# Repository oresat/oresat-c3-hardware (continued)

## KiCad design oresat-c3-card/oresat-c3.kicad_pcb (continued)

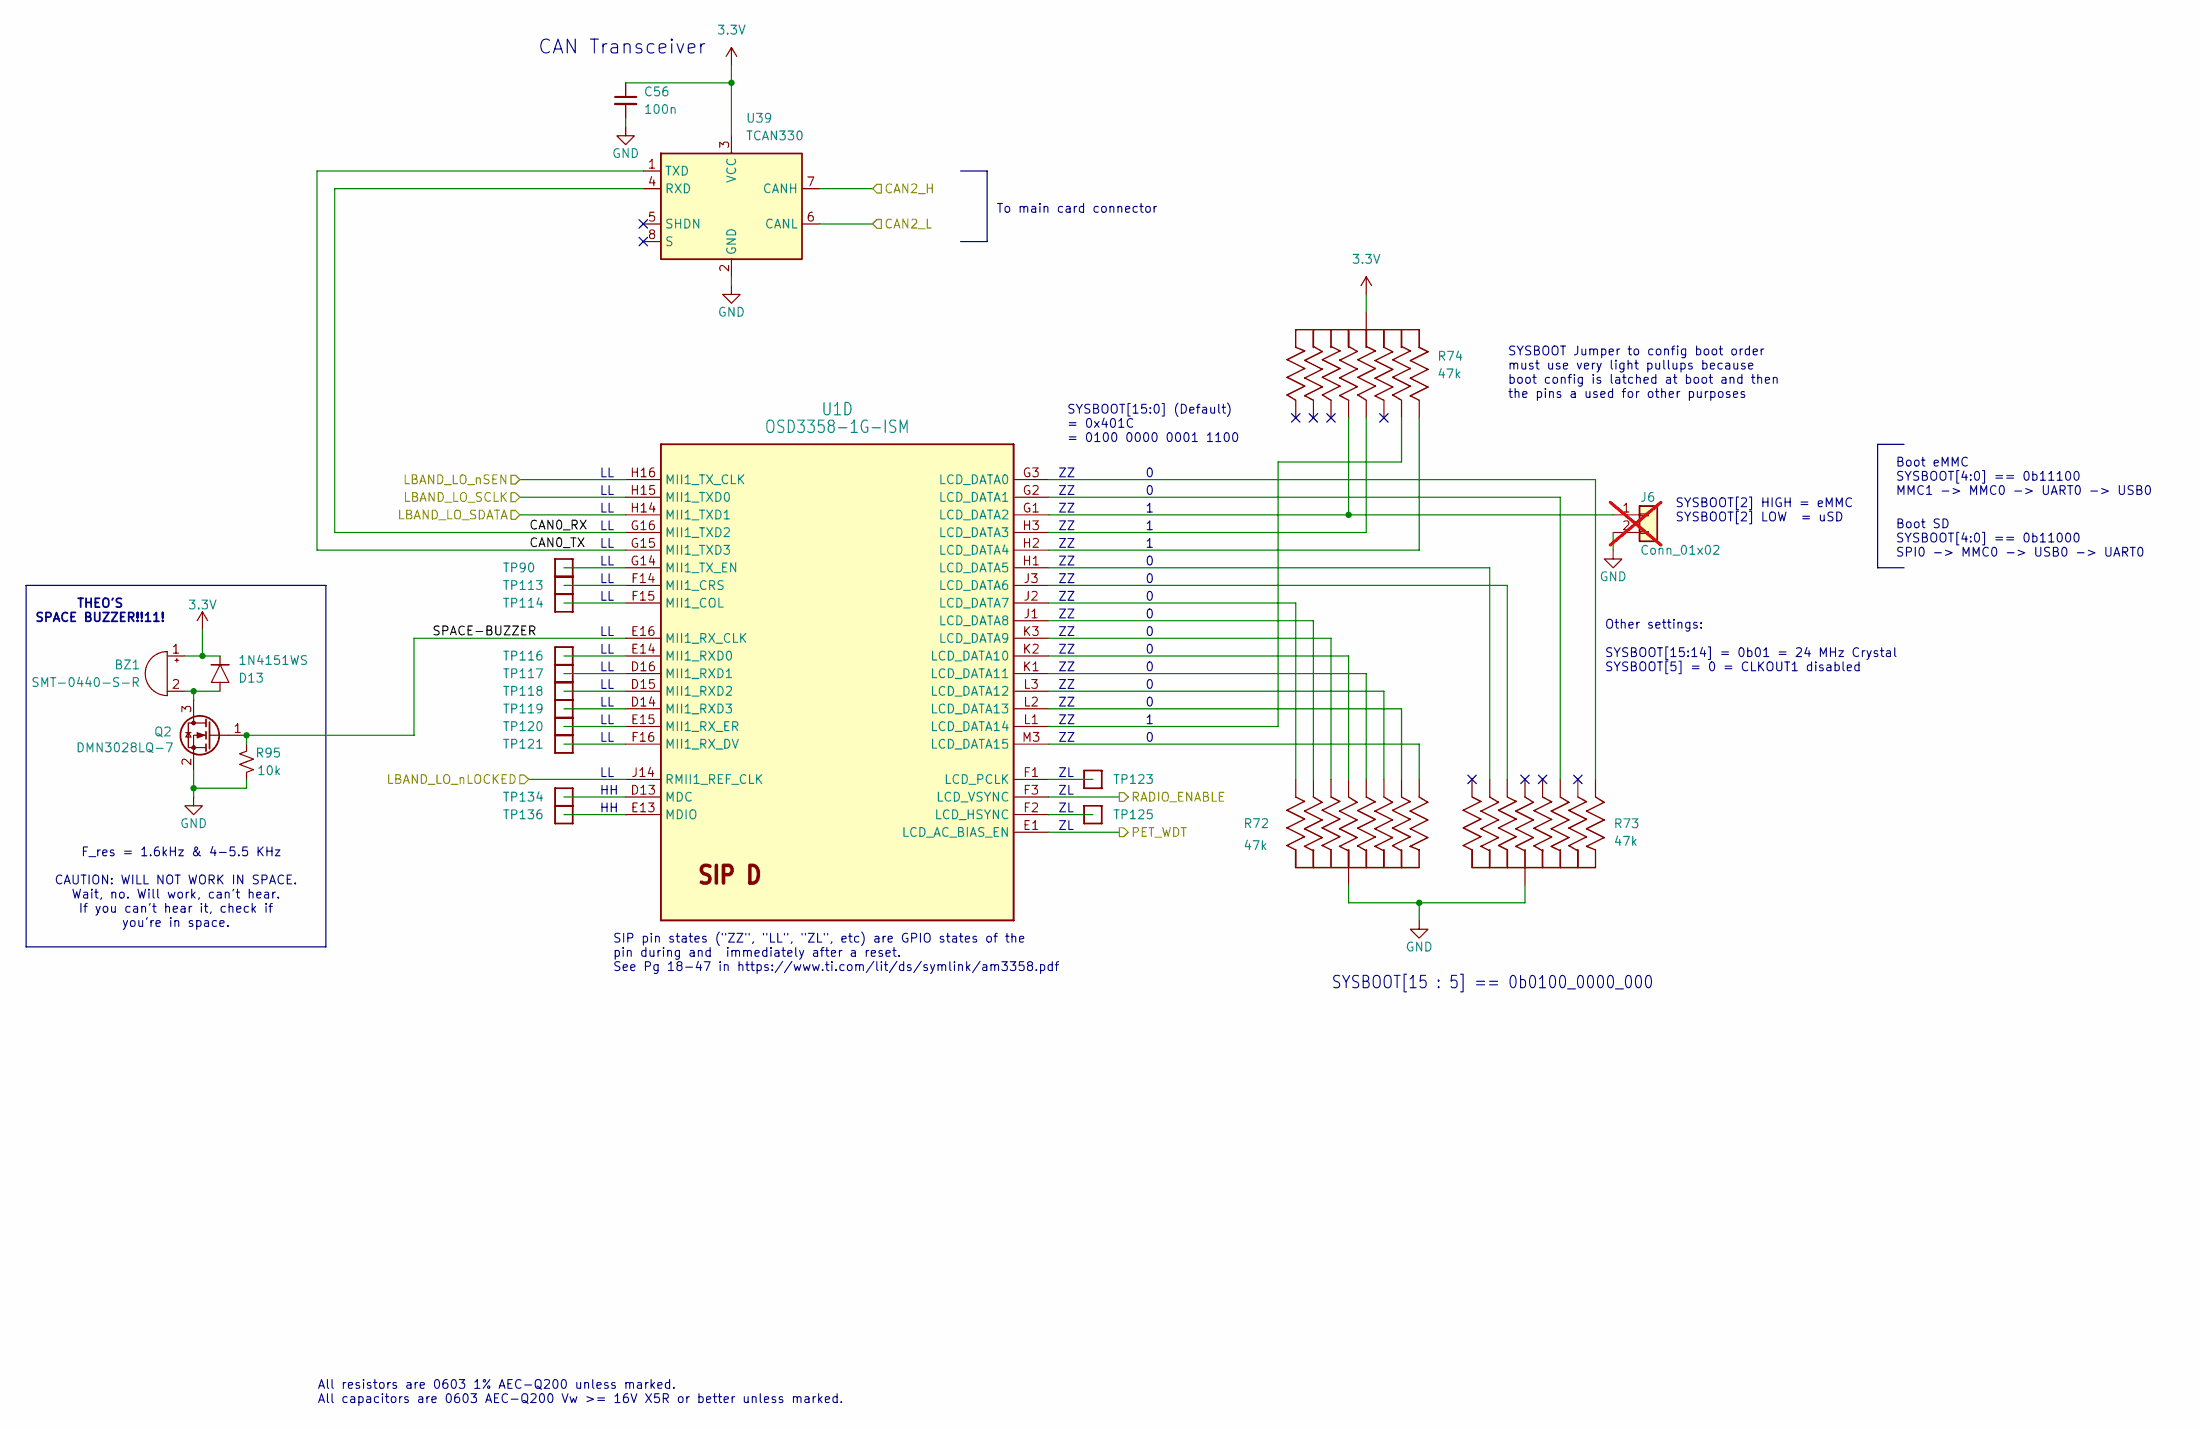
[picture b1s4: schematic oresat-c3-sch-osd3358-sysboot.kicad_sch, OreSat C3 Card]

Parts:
BZ1: SMT-0440-S-R; MPN SMT-0440-S-R
C56: 100n; 0603-C-NOSILK; MPN C0603C104K5RACAUTO
D13: 1N4151WS; D_SOD-323; MPN 1N4151WS-E3-08
J6: Conn_01x02; PinHeader_1x02_P2.54mm_Vertical; not fitted
Q2: DMN3028LQ-7; SOT-23-3; MPN DMN3028LQ-7
R72, R73, R74: 47k; Panasonic_Resistor_Array_EXBA10; MPN EXB-A10P473J
R95: 10k; 0603-C-NOSILK; MPN RMCF0603FT10K0
TP90, TP113, TP114, TP116, TP117, TP118, TP119, TP120, TP121, TP123, TP125, TP134, TP136: Test-Point; TestPoint_Pad_D1.0mm
U1: OSD3358-1G-ISM; U-Octavo-OSD335X-BGA-256; MPN OSD3358-512M-BSM
U39: TCAN330; SOT-23-8; MPN TCAN330GDCNT

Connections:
3.3V: BZ1.1 (+), C56.1, D13.1, R74.5 (55), R74.10 (55), U39.3 (VCC); also elsewhere on the board
/CAN2_H: U39.7 (CANH); also elsewhere on the board
/CAN2_L: U39.6 (CANL); also elsewhere on the board
/L Band/LBAND_LO_SCLK: U1.H15 (MII1_TXD0); also elsewhere on the board
/L Band/LBAND_LO_SDATA: U1.H14 (MII1_TXD1); also elsewhere on the board
/L Band/LBAND_LO_nLOCKED: U1.J14 (RMII1_REF_CLK); also elsewhere on the board
/L Band/LBAND_LO_nSEN: U1.H16 (MII1_TX_CLK); also elsewhere on the board
/OSD3358: SIP D/CAN0_RX: U1.G16 (MII1_TXD2), U39.4 (RXD)
/OSD3358: SIP D/CAN0_TX: U1.G15 (MII1_TXD3), U39.1 (TXD)
/OSD3358: SIP D/PET_WDT: U1.E1 (LCD_AC_BIAS_EN); also elsewhere on the board
/OSD3358: SIP D/RADIO_ENABLE: U1.F3 (LCD_VSYNC); also elsewhere on the board
/OSD3358: SIP D/SPACE-BUZZER: Q2.1 (G), R95.1, U1.E16 (MII1_RX_CLK)
GND: C56.2, J6.2, Q2.2 (S), R72.5 (55), R72.10 (55), R73.5 (55), R73.10 (55), R95.2, U39.2 (GND); also elsewhere on the board
unnamed: BZ1.2 (-), D13.2, Q2.3 (D)
unnamed: J6.1, R74.8 (88), U1.G1 (LCD_DATA2)
unnamed: R72.1 (11), U1.M3 (LCD_DATA15)
unnamed: R72.2 (22), U1.L3 (LCD_DATA12)
unnamed: R72.3 (33), U1.K2 (LCD_DATA10)
unnamed: R72.4 (44), U1.J1 (LCD_DATA8)
unnamed: R72.6 (66), U1.J2 (LCD_DATA7)
unnamed: R72.7 (77), U1.K3 (LCD_DATA9)
unnamed: R72.8 (88), U1.K1 (LCD_DATA11)
unnamed: R72.9 (99), U1.L2 (LCD_DATA13)
unnamed: R73.1 (11), U1.G3 (LCD_DATA0)
unnamed: R73.2 (22), U1.G2 (LCD_DATA1)
unnamed: R73.4 (44), U1.H1 (LCD_DATA5)
unnamed: R73.7 (77), U1.J3 (LCD_DATA6)
unnamed: R74.3 (33), U1.H3 (LCD_DATA3)
unnamed: R74.4 (44), U1.L1 (LCD_DATA14)
unnamed: R74.6 (66), U1.H2 (LCD_DATA4)
unnamed: TP125.1 (1_1), U1.F2 (LCD_HSYNC)
unnamed: TP123.1 (1_1), U1.F1 (LCD_PCLK)
unnamed: TP134.1 (1_1), U1.D13 (MDC)
unnamed: TP136.1 (1_1), U1.E13 (MDIO)
unnamed: TP114.1 (1_1), U1.F15 (MII1_COL)
unnamed: TP113.1 (1_1), U1.F14 (MII1_CRS)
unnamed: TP116.1 (1_1), U1.E14 (MII1_RXD0)
unnamed: TP117.1 (1_1), U1.D16 (MII1_RXD1)
unnamed: TP118.1 (1_1), U1.D15 (MII1_RXD2)
unnamed: TP119.1 (1_1), U1.D14 (MII1_RXD3)
unnamed: TP121.1 (1_1), U1.F16 (MII1_RX_DV)
unnamed: TP120.1 (1_1), U1.E15 (MII1_RX_ER)
unnamed: TP90.1 (1_1), U1.G14 (MII1_TX_EN)

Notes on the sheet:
THEO'S SPACE BUZZER!!11!
SYSBOOT[2] HIGH = eMMC SYSBOOT[2] LOW = uSD
SIP pin states ("ZZ", "LL", "ZL", etc) are GPIO states of the pin during and immediately after a reset. See Pg 18-47 in https://www.ti.com/lit/ds/symlink/am3358.pdf
Boot SD SYSBOOT[4:0] == 0b11000 SPI0 -> MMC0 -> USB0 -> UART0
All resistors are 0603 1% AEC-Q200 unless marked. All capacitors are 0603 AEC-Q200 Vw >= 16V X5R or better unless marked.
Boot eMMC SYSBOOT[4:0] == 0b11100 MMC1 -> MMC0 -> UART0 -> USB0
SYSBOOT[15:0] (Default) = 0x401C = 0100 0000 0001 1100
CAN Transceiver
SYSBOOT Jumper to config boot order must use very light pullups because boot config is latched at boot and then the pins a used for other purposes
F_res = 1.6kHz & 4-5.5 KHz
Other settings: SYSBOOT[15:14] = 0b01 = 24 MHz Crystal SYSBOOT[5] = 0 = CLKOUT1 disabled
SYSBOOT[15 : 5] == 0b0100_0000_000
To main card connector
CAUTION: WILL NOT WORK IN SPACE. Wait, no. Will work, can't hear. If you can't hear it, check if you're in space.

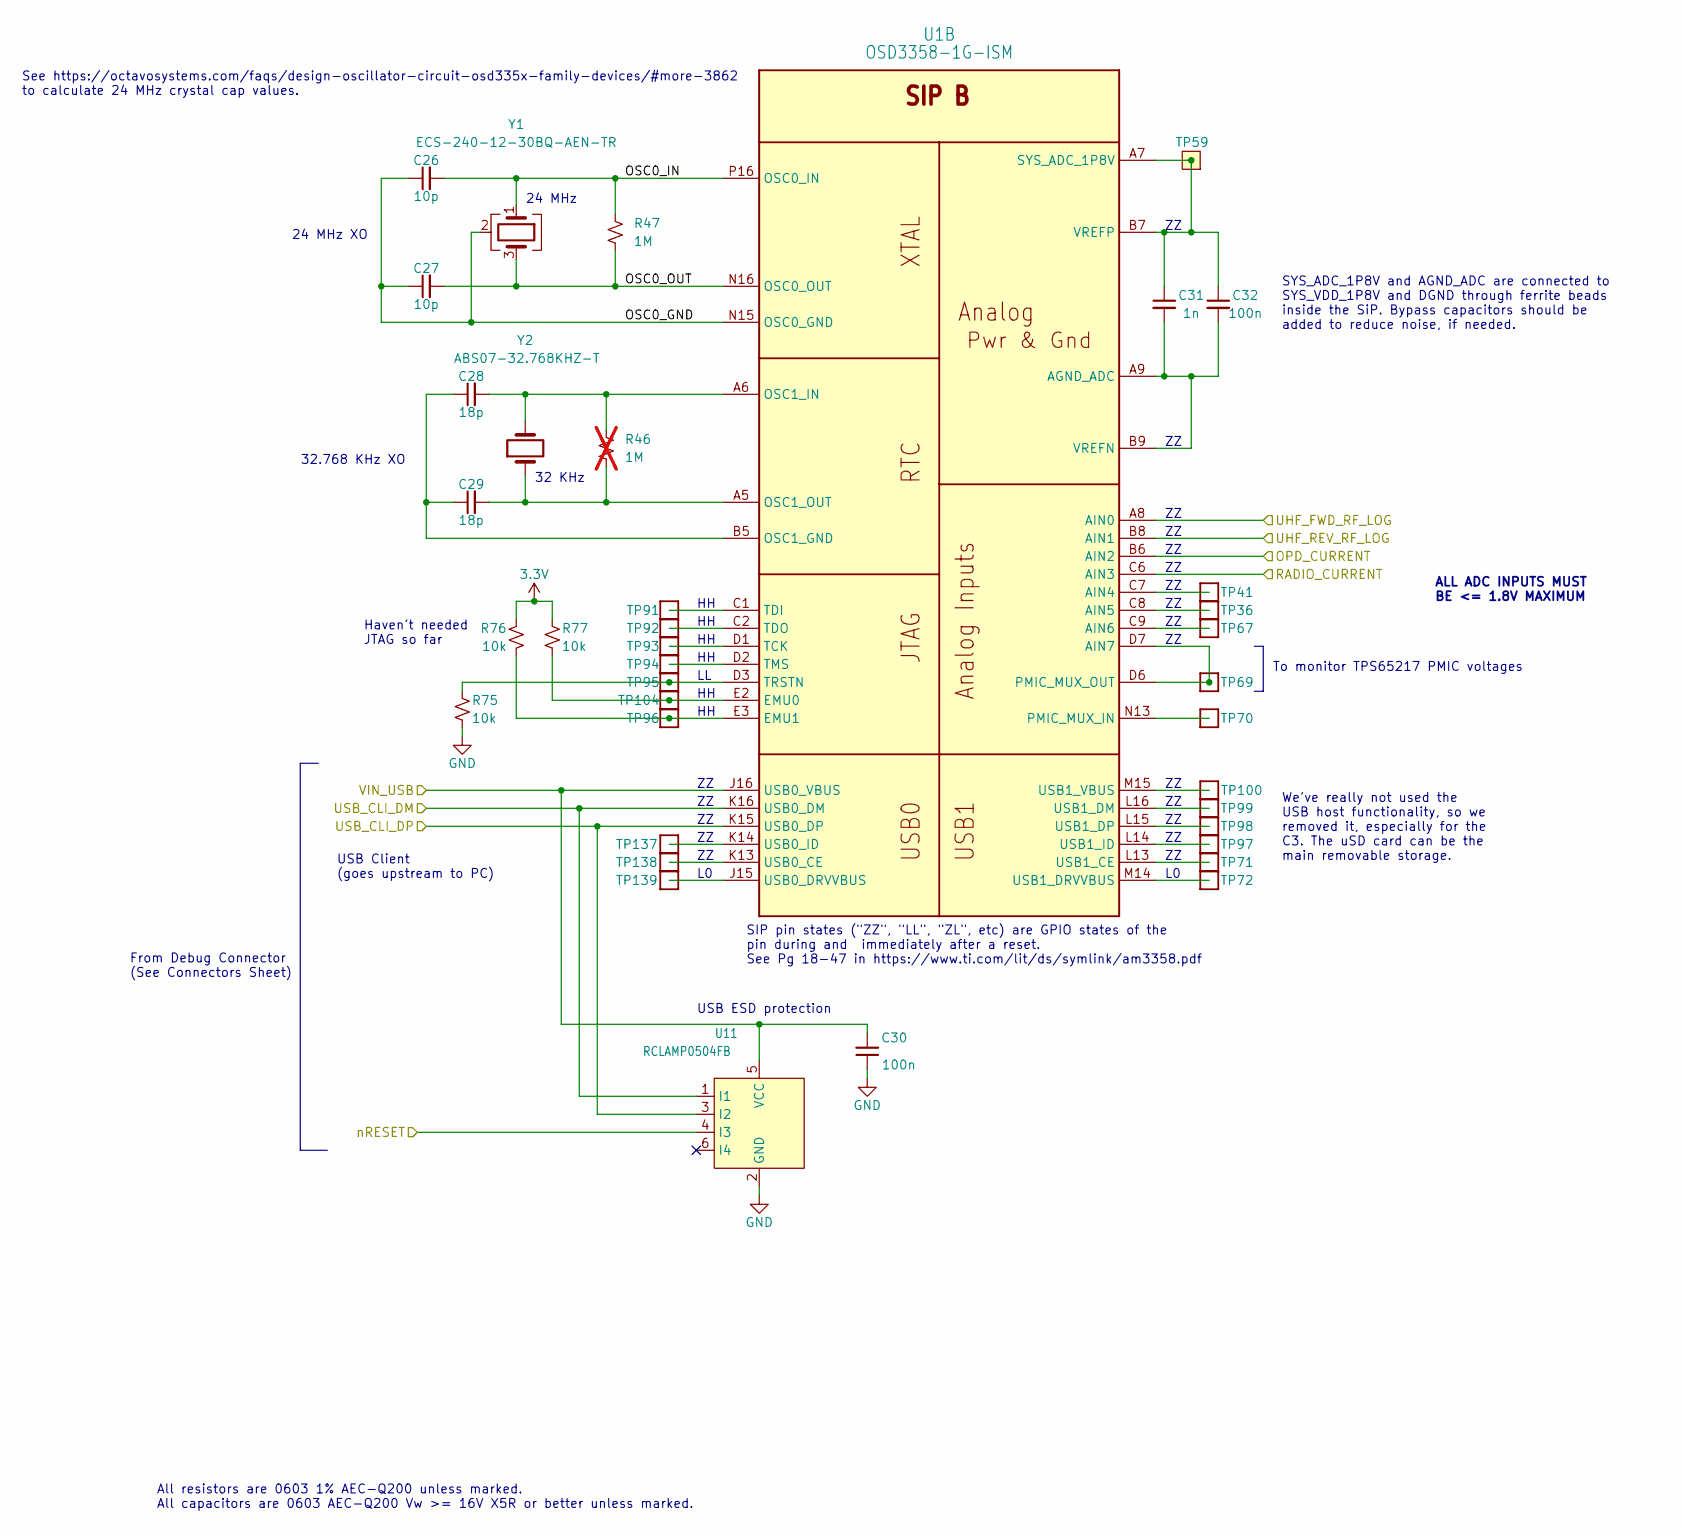
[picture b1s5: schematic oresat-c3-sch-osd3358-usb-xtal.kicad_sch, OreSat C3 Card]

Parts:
C26, C27: 10p; 0603-C-NOSILK; MPN C0603C100J1GACAUTO
C28, C29: 18p; 0603-C-NOSILK; MPN C0603C180F5GACAUTO
C30, C32: 100n; 0603-C-NOSILK; MPN C0603C104K5RACAUTO
C31: 1n; 0603-C-NOSILK; MPN C0603C102J5RACAUTO
R46: 1M; R_0603_1608Metric; not fitted
R47: 1M; 0603-C-NOSILK; MPN RMCF0603FG1M00
R75, R76, R77: 10k; 0603-C-NOSILK; MPN RMCF0603FT10K0
TP36, TP41, TP67, TP69, TP70, TP71, TP72, TP91, TP92, TP93, TP94, TP95, TP96, TP97, TP98, TP99, TP100, TP104, TP137, TP138, TP139: Test-Point; TestPoint_Pad_D1.0mm
TP59: Test-Point; TestPoint-0.75mm-th
U1: OSD3358-1G-ISM; U-Octavo-OSD335X-BGA-256; MPN OSD3358-512M-BSM
U11: RCLAMP0504FB; SOT-363_SC-70-6; MPN RCLAMP0504FBTCT
Y1: ECS-240-12-30BQ-AEN-TR; CRYSTAL-5X3.2-4SMD; MPN ECS-240-12-30BQ-AEN-TR
Y2: ABS07-32.768KHZ-T; CRYSTAL_3.2X1.5; MPN ABS07-32.768KHZ-T

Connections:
3.3V: R76.1, R77.1; also elsewhere on the board
/OPD and I2C Peripherals/OPD_CURRENT: U1.B6 (AIN2); also elsewhere on the board
/OSD3358: SIP A/nRESET: U11.4 (I3); also elsewhere on the board
/OSD3358: SIP B/OSC0_GND: C26.1, C27.1, U1.N15 (OSC0_GND), Y1.2 (G), Y1.4 (G)
/OSD3358: SIP B/OSC0_IN: C26.2, R47.1, U1.P16 (OSC0_IN), Y1.1
/OSD3358: SIP B/OSC0_OUT: C27.2, R47.2, U1.N16 (OSC0_OUT), Y1.3
/OSD3358: SIP B/RADIO_CURRENT: U1.C6 (AIN3); also elsewhere on the board
/OSD3358: SIP B/UHF_FWD_RF_LOG: U1.A8 (AIN0); also elsewhere on the board
/OSD3358: SIP B/UHF_REV_RF_LOG: U1.B8 (AIN1); also elsewhere on the board
/USB_CLI_DM: U1.K16 (USB0_DM), U11.1 (I1); also elsewhere on the board
/USB_CLI_DP: U1.K15 (USB0_DP), U11.3 (I2); also elsewhere on the board
/VIN_USB: C30.2, U1.J16 (USB0_VBUS), U11.5 (VCC); also elsewhere on the board
GND: C30.1, R75.2, U11.2 (GND); also elsewhere on the board
unnamed: C31.2, C32.2, U1.A9 (AGND_ADC), U1.B9 (VREFN)
unnamed: TP41.1 (1_1), U1.C7 (AIN4)
unnamed: TP36.1 (1_1), U1.C8 (AIN5)
unnamed: TP67.1 (1_1), U1.C9 (AIN6)
unnamed: TP69.1 (1_1), U1.D6 (PMIC_MUX_OUT), U1.D7 (AIN7)
unnamed: R77.2, TP95.1 (1_1), U1.E2 (EMU0)
unnamed: R76.2, TP96.1 (1_1), U1.E3 (EMU1)
unnamed: C28.1, C29.1, U1.B5 (OSC1_GND)
unnamed: C28.2, R46.1, U1.A6 (OSC1_IN), Y2.2
unnamed: C29.2, R46.2, U1.A5 (OSC1_OUT), Y2.1
unnamed: TP70.1 (1_1), U1.N13 (PMIC_MUX_IN)
unnamed: C31.1, C32.1, TP59.1 (1_1), U1.A7 (SYS_ADC_1P8V), U1.B7 (VREFP)
unnamed: TP93.1 (1_1), U1.D1 (TCK)
unnamed: TP91.1 (1_1), U1.C1 (TDI)
unnamed: TP92.1 (1_1), U1.C2 (TDO)
unnamed: TP94.1 (1_1), U1.D2 (TMS)
unnamed: R75.1, TP104.1 (1_1), U1.D3 (TRSTN)
unnamed: TP138.1 (1_1), U1.K13 (USB0_CE)
unnamed: TP139.1 (1_1), U1.J15 (USB0_DRVVBUS)
unnamed: TP137.1 (1_1), U1.K14 (USB0_ID)
unnamed: TP71.1 (1_1), U1.L13 (USB1_CE)
unnamed: TP99.1 (1_1), U1.L16 (USB1_DM)
unnamed: TP98.1 (1_1), U1.L15 (USB1_DP)
unnamed: TP72.1 (1_1), U1.M14 (USB1_DRVVBUS)
unnamed: TP97.1 (1_1), U1.L14 (USB1_ID)
unnamed: TP100.1 (1_1), U1.M15 (USB1_VBUS)

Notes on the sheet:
32.768 KHz XO
ALL ADC INPUTS MUST BE <= 1.8V MAXIMUM
To monitor TPS65217 PMIC voltages
SIP pin states ("ZZ", "LL", "ZL", etc) are GPIO states of the pin during and immediately after a reset. See Pg 18-47 in https://www.ti.com/lit/ds/symlink/am3358.pdf
See https://octavosystems.com/faqs/design-oscillator-circuit-osd335x-family-devices/#more-3862 to calculate 24 MHz crystal cap values.
24 MHz XO
32 KHz
Haven't needed JTAG so far
All resistors are 0603 1% AEC-Q200 unless marked. All capacitors are 0603 AEC-Q200 Vw >= 16V X5R or better unless marked.
We've really not used the USB host functionality, so we removed it, especially for the C3. The uSD card can be the main removable storage.
USB Client (goes upstream to PC)
24 MHz
USB ESD protection
SYS_ADC_1P8V and AGND_ADC are connected to SYS_VDD_1P8V and DGND through ferrite beads inside the SiP. Bypass capacitors should be added to reduce noise, if needed.
From Debug Connector (See Connectors Sheet)

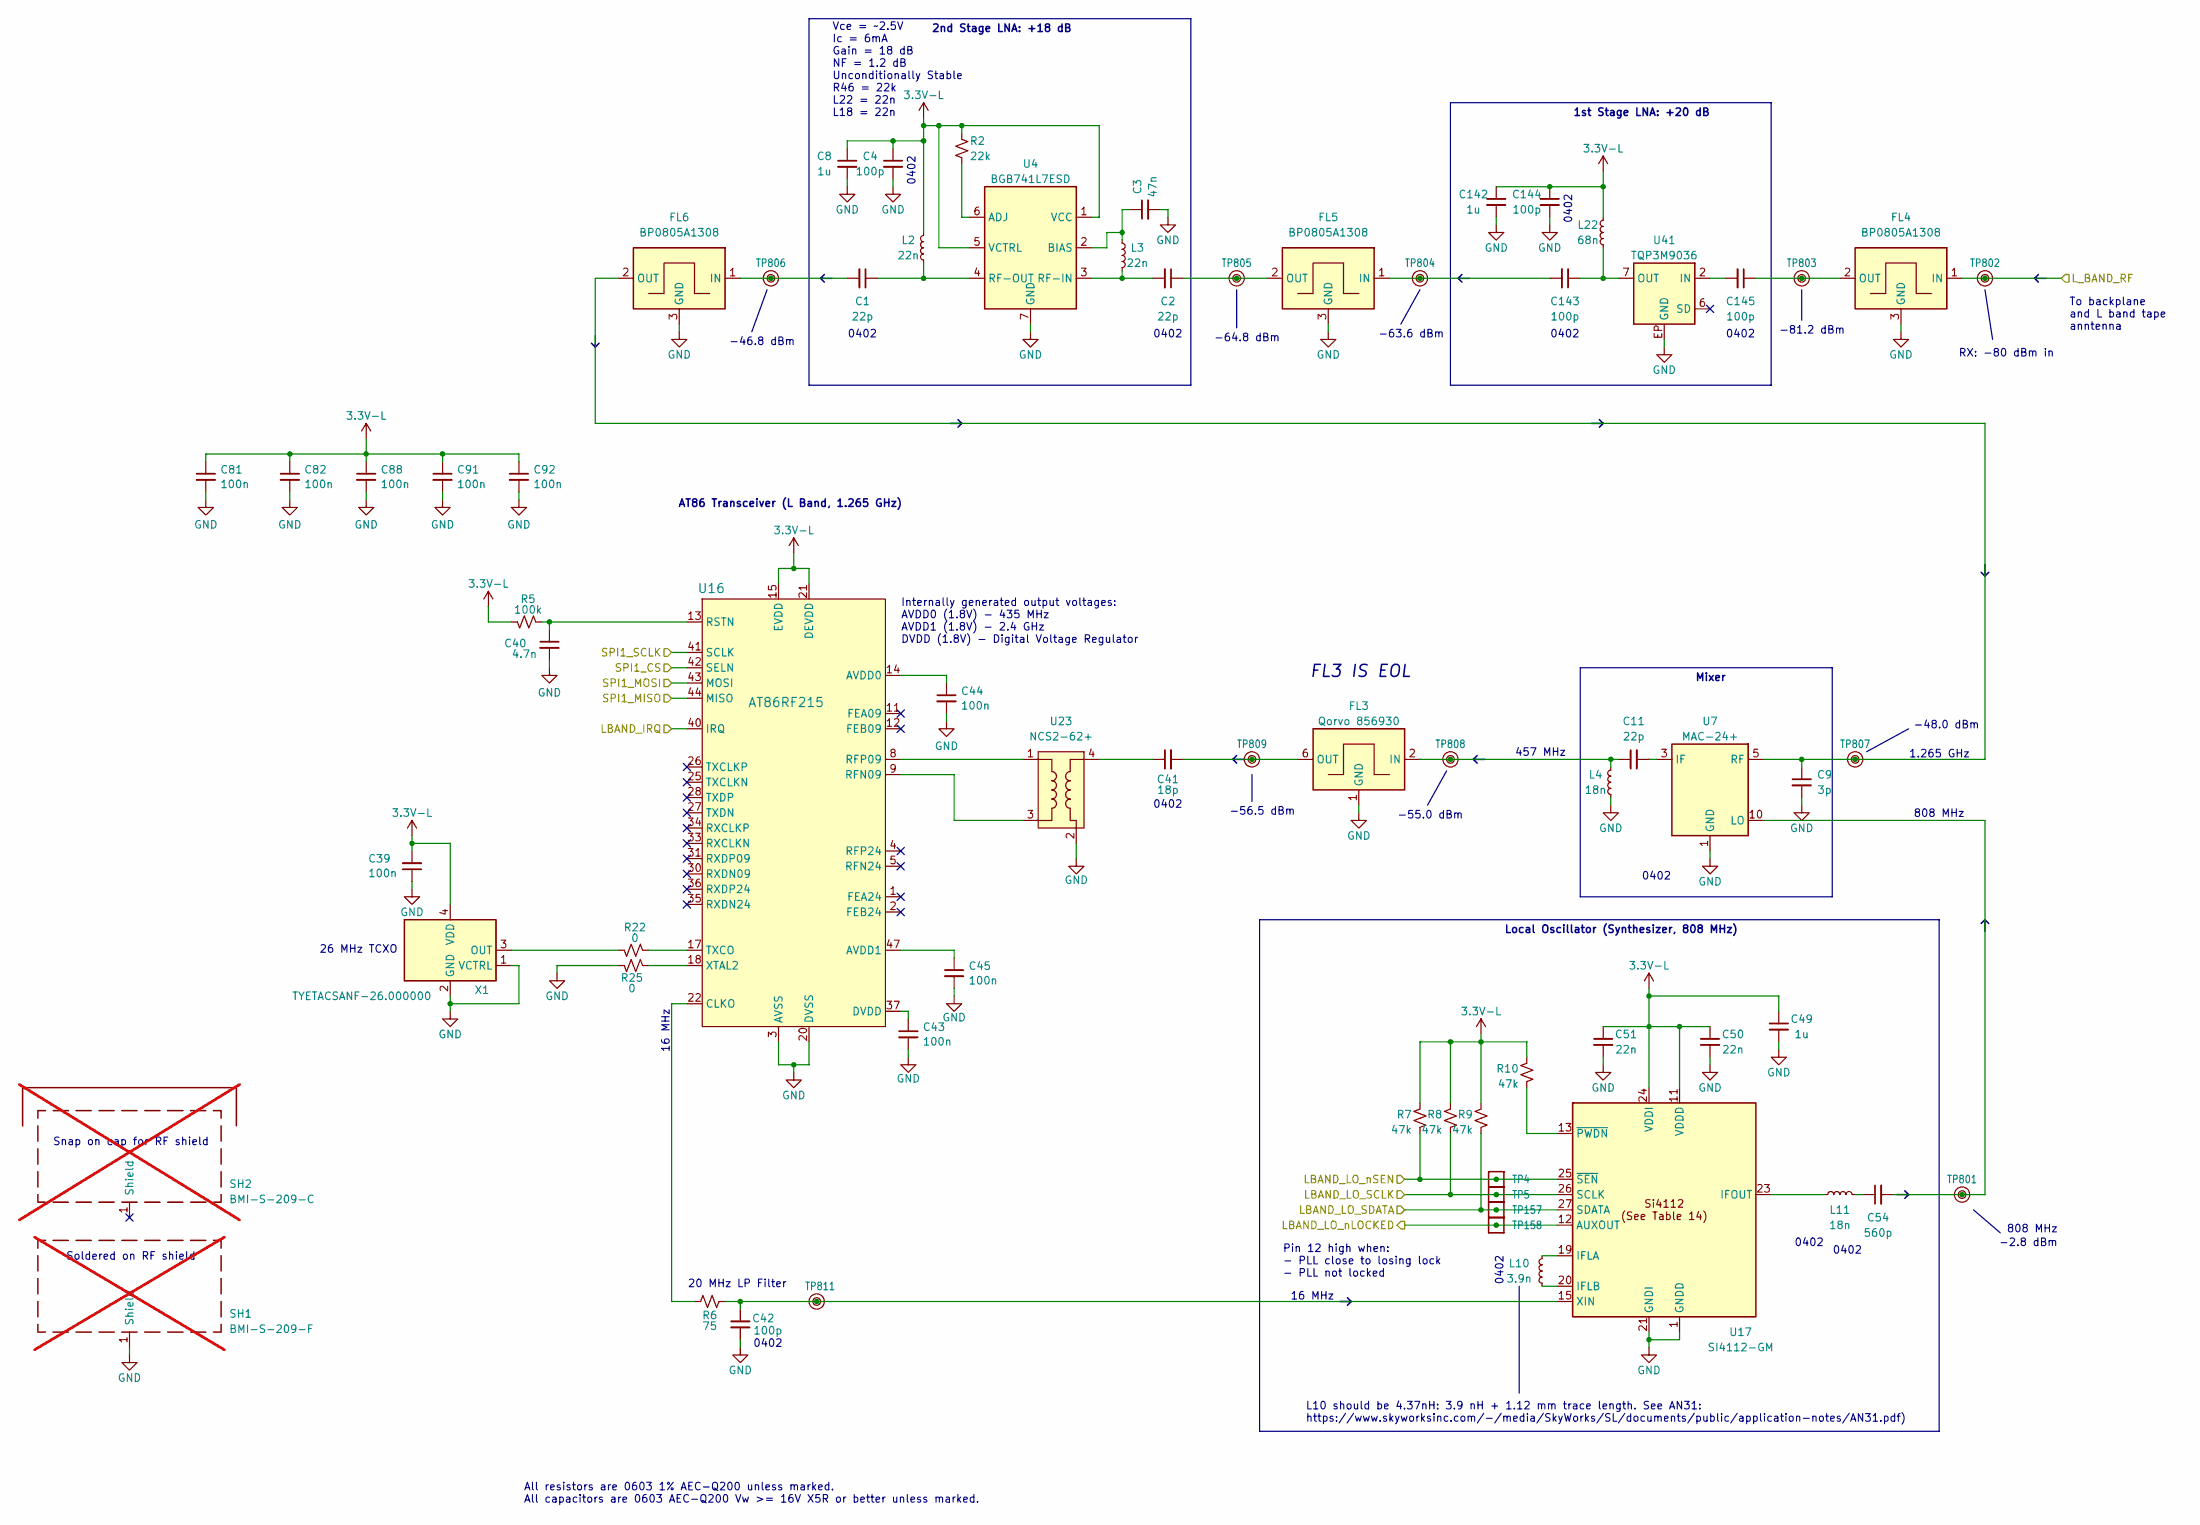
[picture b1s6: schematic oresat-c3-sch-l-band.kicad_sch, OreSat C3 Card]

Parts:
C1, C2, C11: 22p; 0402-B-NOSILK; MPN CBR04C220J5GACAUTO
C3: 47n; 0603-C-NOSILK; MPN C0603C473K5RACAUTO
C4, C42, C143, C144, C145: 100p; 0402-B-NOSILK; MPN C0402C101J5GACAUTO
C8, C49, C142: 1u; 0603-C-NOSILK; MPN GRT188R71E105KE13D
C9: 3p; 0402-B-NOSILK; MPN GCQ1555C1H3R0CB01D
C39, C43, C44, C45, C81, C82, C88, C91, C92: 100n; 0603-C-NOSILK; MPN C0603C104K5RACAUTO
C40: 4.7n; 0603-C-NOSILK; MPN C0603C472K5RACAUTO
C41: 18p; 0402-B-NOSILK; MPN CBR04C180J5GACAUTO
C50, C51: 22n; 0603-C-NOSILK; MPN C0603C223K1RACAUTO
C54: 560p; 0402-B-NOSILK; MPN C0402C561J5GACAUTO
FL3: Qorvo 856930; 856930-saw-filter; MPN 856930
FL4, FL5, FL6: BP0805A1308; BP0805; MPN BP0805A1308ASTR
L2, L3: 22n; L_0603_1608Metric; MPN LQW18AN22NG0ZD
L4, L11: 18n; L_0402_1005Metric; MPN 0402HP-18NXGL
L10: 3.9n; L_0402_1005Metric; MPN 0402CS-3N9XGL
L22: 68n; L_0603_1608Metric; MPN LQW18AN68NG8ZD
R2: 22k; 0603-C-NOSILK; MPN RMCF0603FT22K0
R5: 100k; 0603-C-NOSILK; MPN RMCF0603FT100K
R6: 75; 0603-C-NOSILK; MPN RMCF0603FT75R0
R7, R8, R9, R10: 47k; 0603-C-NOSILK; MPN RMCF0603FT47K0
R22, R25: 0; 0603-C-NOSILK; MPN RMCF0603ZT0R00
SH1: BMI-S-209-F; Laird_Technologies_BMI-S-209-F_29.36x18.50mm; MPN BMI-S-209-F; not fitted
SH2: BMI-S-209-C; MPN BMI-S-209-C; not fitted
TP4, TP5, TP157, TP158: Test-Point; TestPoint_Pad_D1.0mm
TP801, TP802, TP803, TP804, TP805, TP806, TP807, TP808, TP809, TP811: TestPoint_RF_Probe
U4: BGB741L7ESD; Infineon-PG-TSLP-7-LNA; MPN BGB741L7ESDE6327XTSA1‎
U7: MAC-24+; MPN MAC-24+
U16: AT86RF215; QFN-48-1EP_7x7mm_P0.5mm_EP5.6x5.6mm; MPN AT86RF215-ZUR
U17: SI4112-GM; QFN-28-1EP_5x5mm_P0.5mm_EP3.35x3.35mm_ThermalVias; MPN SI4112-D-GM
U23: NCS2-62+; 2450FB15A050E_JOT; MPN NCS2-62+
U41: TQP3M9036; U-Qorvo-TQP3M9036-QFN-8-MO-220E; MPN TQP3M9036
X1: TYETACSANF-26.000000; X_TCXO_SMD_Taitien_2.5x2.0mm; MPN TYETACSANF-26.000000

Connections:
3.3V-L: C4.1, C8.1, C39.2, C49.1, C50.1, C51.1, C81.1, C82.1, C88.1, C91.1, C92.1, C142.1, C144.1, L2.1, L22.1, R2.1, R5.2, R7.1, R8.1, R9.1, R10.1, U4.1 (VCC), U4.5 (VCTRL), U16.15 (EVDD), U16.21 (DEVDD), U16.29 (DEVDD), U16.39 (DEVDD), U16.46 (EVDD), U17.11 (VDDD), U17.17 (VDDD), U17.24 (VDDI), X1.4 (VDD); also elsewhere on the board
/L Band/LBAND_IRQ: U16.40 (IRQ); also elsewhere on the board
/L Band/LBAND_LO_SCLK: R8.2, TP5.1 (1_1), U17.26 (SCLK); also elsewhere on the board
/L Band/LBAND_LO_SDATA: R9.2, TP157.1 (1_1), U17.27 (SDATA); also elsewhere on the board
/L Band/LBAND_LO_nLOCKED: TP158.1 (1_1), U17.12 (AUXOUT); also elsewhere on the board
/L Band/LBAND_LO_nSEN: R7.2, TP4.1 (1_1), U17.25 (~SEN); also elsewhere on the board
/L Band/SPI1_CS: U16.42 (SELN); also elsewhere on the board
/L Band/SPI1_MISO: U16.44 (MISO); also elsewhere on the board
/L Band/SPI1_MOSI: U16.43 (MOSI); also elsewhere on the board
/L Band/SPI1_SCLK: U16.41 (SCLK); also elsewhere on the board
/L_BAND_RF: FL4.1 (IN), TP802.1 (1_1); also elsewhere on the board
GND: C3.2, C4.2, C8.2, C9.2, C39.1, C40.2, C42.2, C43.2, C44.2, C45.2, C49.2, C50.2, C51.2, C81.2, C82.2, C88.2, C91.2, C92.2, C142.2, C144.2, FL3.1 (GND), FL3.3 (GND), FL3.4 (GND), FL3.5 (GND), FL3.7 (GND), FL3.8 (GND), FL4.3 (GND), FL4.4 (GND), FL5.3 (GND), FL5.4 (GND), FL6.3 (GND), FL6.4 (GND), L4.2, R25.2, SH1.1 (Shield_1), U4.7 (GND), U7.1 (GND), U7.2 (GND), U7.4 (GND), U7.6 (GND), U7.7 (GND), U7.8 (GND), U7.9 (GND), U16.3 (AVSS), U16.6 (AVSS), U16.7 (AVSS), U16.10 (AVSS), U16.16 (AVSS), U16.19 (AVSS), U16.20 (DVSS), U16.23 (DVSS), U16.24 (DVSS), U16.32 (DVSS), U16.38 (DVSS), U16.45 (AVSS), U16.48 (AVSS), U16.49 (AVSS), U17.1 (GNDD), U17.2 (GNDD), U17.3 (GNDD), U17.4 (GNDD), U17.5 (GNDD), U17.6 (GNDD), U17.7 (GNDD), U17.8 (GNDD), U17.9 (GNDD), U17.10 (GNDD), U17.14 (GNDD), U17.16 (GNDD), U17.18 (GNDD), U17.21 (GNDI), U17.22 (GNDI), U17.28 (GNDD), U17.29 (GNDD), U23.2 (GND), U23.6 (GND), U41.EP (GND), X1.1 (VCTRL), X1.2 (GND); also elsewhere on the board
unnamed: C41.1, U23.4
unnamed: C54.1, L11.2
unnamed: C11.1, FL3.2 (IN), L4.1, TP808.1 (1_1)
unnamed: C41.2, FL3.6 (OUT), TP809.1 (1_1)
unnamed: C145.1, FL4.2 (OUT), TP803.1 (1_1)
unnamed: C143.2, FL5.1 (IN), TP804.1 (1_1)
unnamed: C2.1, FL5.2 (OUT), TP805.1 (1_1)
unnamed: C1.2, FL6.1 (IN), TP806.1 (1_1)
unnamed: C9.1, FL6.2 (OUT), TP807.1 (1_1), U7.5 (RF)
unnamed: R2.2, U4.6 (ADJ)
unnamed: C3.1, L3.1, U4.2 (BIAS)
unnamed: C2.2, L3.2, U4.3 (RF-IN)
unnamed: C1.1, L2.2, U4.4 (RF-OUT)
unnamed: C11.2, U7.3 (IF)
unnamed: C54.2, TP801.1 (1_1), U7.10 (LO)
unnamed: C44.1, U16.14 (AVDD0)
unnamed: C45.1, U16.47 (AVDD1)
unnamed: R6.1, U16.22 (CLKO)
unnamed: C43.1, U16.37 (DVDD)
unnamed: U16.9 (RFN09), U23.3
unnamed: U16.8 (RFP09), U23.1
unnamed: C40.1, R5.1, U16.13 (RSTN)
unnamed: R22.1, U16.17 (TXCO)
unnamed: R25.1, U16.18 (XTAL2)
unnamed: L10.1, U17.19 (IFLA)
unnamed: L10.2, U17.20 (IFLB)
unnamed: L11.1, U17.23 (IFOUT)
unnamed: C42.1, R6.2, TP811.1 (1_1), U17.15 (XIN)
unnamed: R10.2, U17.13 (~PWDN)
unnamed: C145.2, U41.2 (IN)
unnamed: C143.1, L22.2, U41.7 (OUT)
unnamed: R22.2, X1.3 (OUT)

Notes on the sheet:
0402
-56.5 dBm
-46.8 dBm
Pin 12 high when: - PLL close to losing lock - PLL not locked
RX: -80 dBm in
FL3 IS EOL
AT86 Transceiver (L Band, 1.265 GHz)
Internally generated output voltages: AVDD0 (1.8V) - 435 MHz AVDD1 (1.8V) - 2.4 GHz DVDD (1.8V) - Digital Voltage Regulator
Vce = ~2.5V Ic = 6mA Gain = 18 dB NF = 1.2 dB Unconditionally Stable R46 = 22k L22 = 22n L18 = 22n
L10 should be 4.37nH: 3.9 nH + 1.12 mm trace length. See AN31: https://www.skyworksinc.com/-/media/SkyWorks/SL/documents/public/application-notes/AN31.pdf)
2nd Stage LNA: +18 dB
1.265 GHz
-2.8 dBm
808 MHz
1st Stage LNA: +20 dB
26 MHz TCXO
-81.2 dBm
To backplane and L band tape anntenna
All resistors are 0603 1% AEC-Q200 unless marked. All capacitors are 0603 AEC-Q200 Vw >= 16V X5R or better unless marked.
457 MHz
-55.0 dBm
-64.8 dBm
20 MHz LP Filter
-63.6 dBm
16 MHz
Snap on cap for RF shield
Mixer
Local Oscillator (Synthesizer, 808 MHz)
Soldered on RF shield
-48.0 dBm

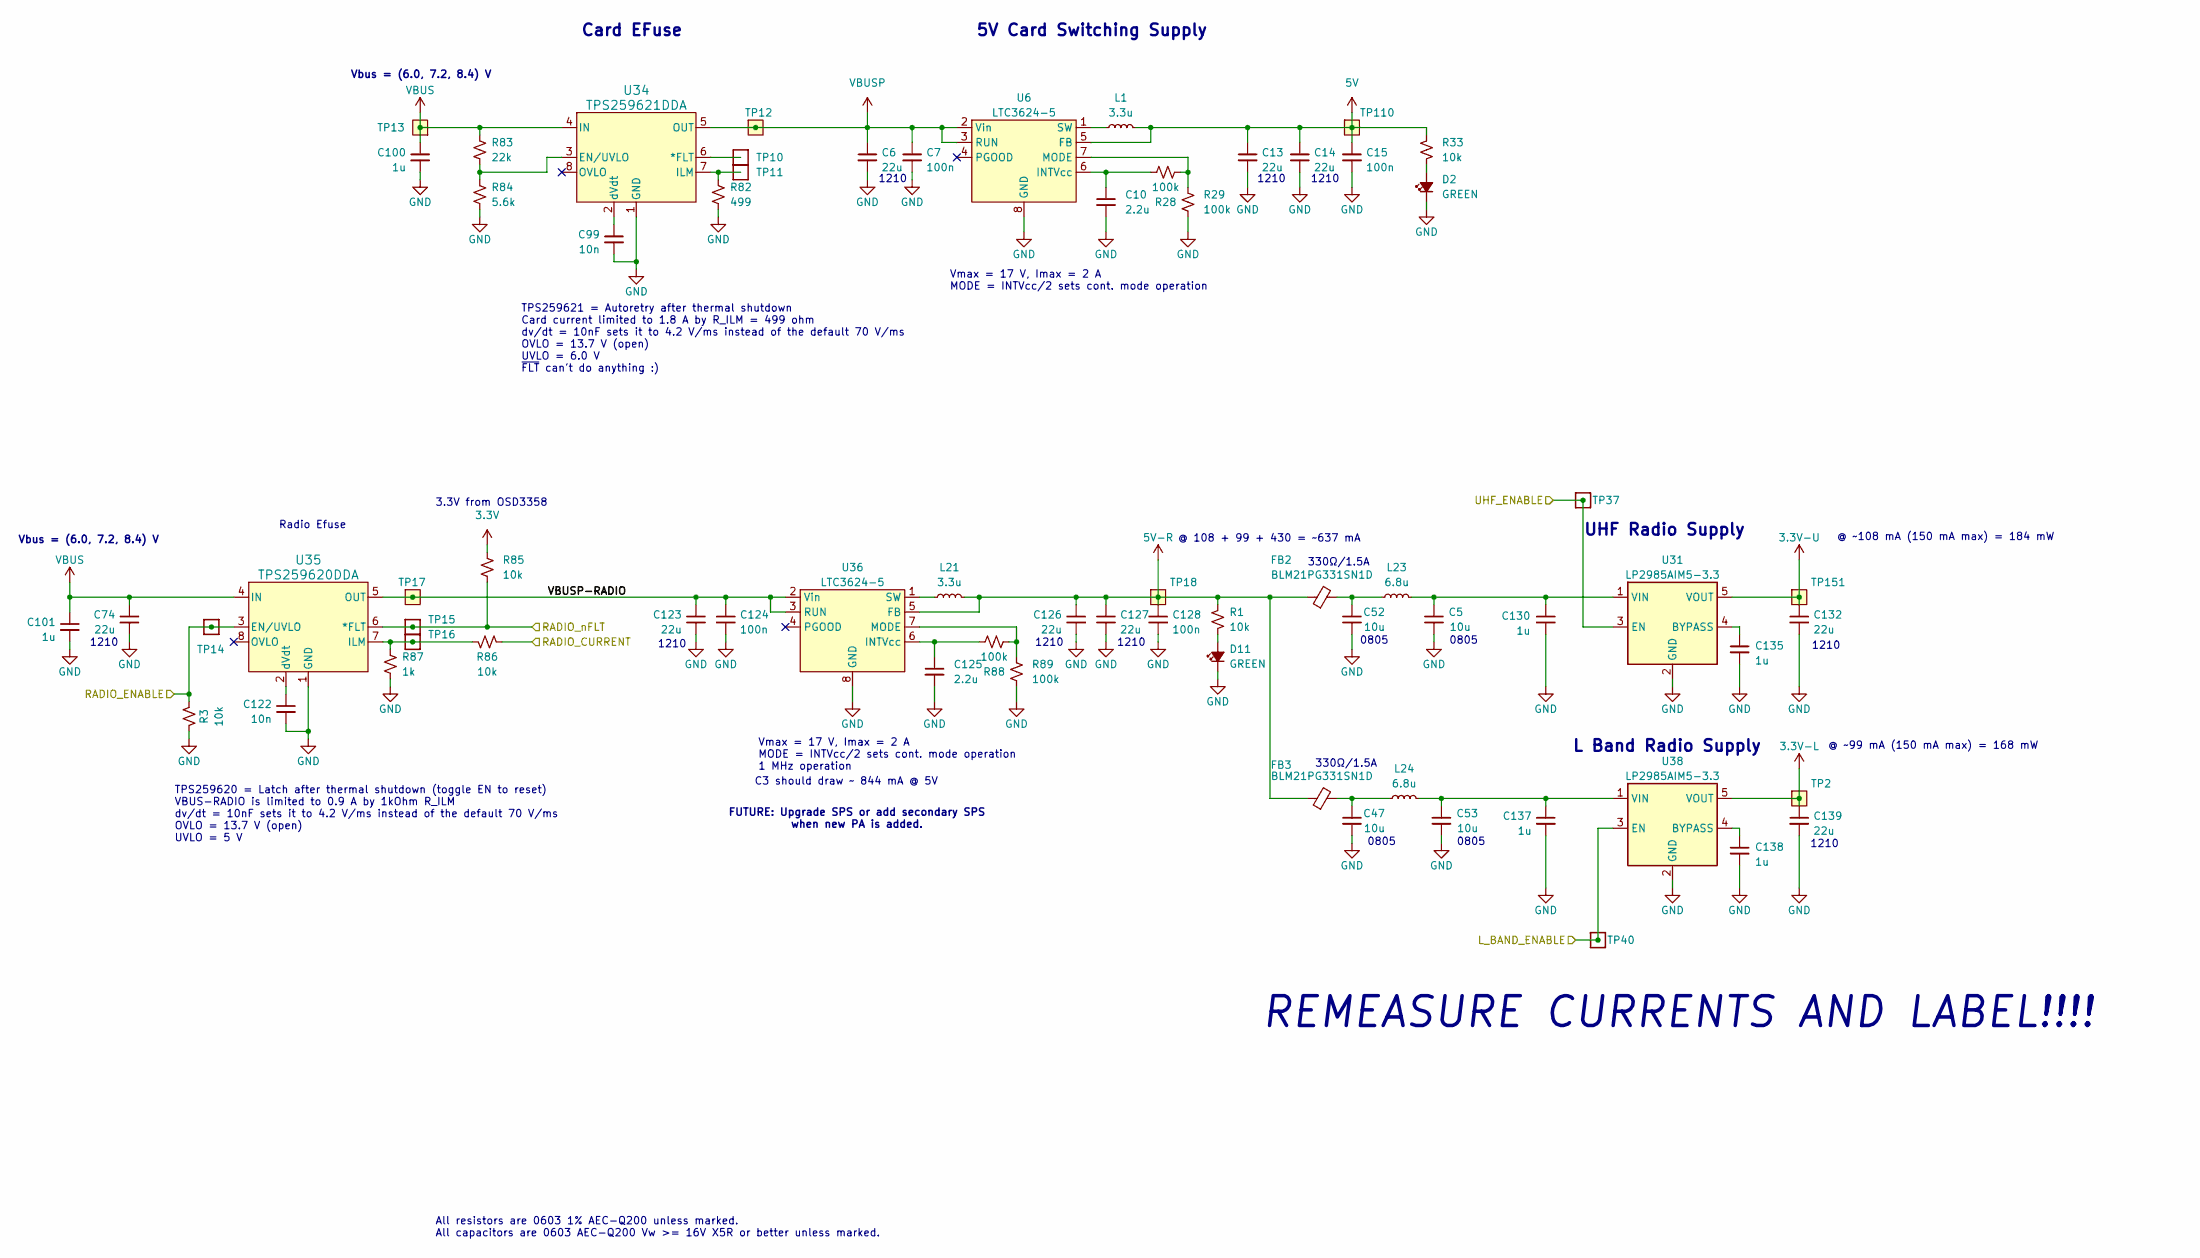
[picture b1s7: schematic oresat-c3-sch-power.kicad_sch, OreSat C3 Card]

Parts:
C5, C47, C52, C53: 10u; 0805-C-NOSILK; MPN GRT21BC71E106KE13K
C6, C13, C14, C74, C123, C126, C127, C132, C139: 22u; C_1210_3225Metric; MPN TMK325B7226KMHP
C7, C15, C124, C128: 100n; 0603-C-NOSILK; MPN C0603C104K5RACAUTO
C10, C125: 2.2u; 0603-C-NOSILK; MPN GRT188C71E225KE13D
C99, C122: 10n; 0603-C-NOSILK; MPN C0603C103J5RACAUTO
C100, C101, C130, C135, C137, C138: 1u; 0603-C-NOSILK; MPN GRT188R71E105KE13D
D2, D11: GREEN; LED_0603_1608Metric; MPN 150060GS75000
FB2, FB3: BLM21PG331SN1D; R_0805_2012Metric; MPN BLM21PG331SN1D
L1, L21: 3.3u; L_ECS-MPI4040; MPN ECS-MPI4040R3-3R3-R
L23, L24: 6.8u; L_ECS-MPI4040; MPN ECS-MPI4040R4-6R8-R
R1, R3, R33, R85, R86: 10k; 0603-C-NOSILK; MPN RMCF0603FT10K0
R28, R29, R88, R89: 100k; 0603-C-NOSILK; MPN RMCF0603FT100K
R82: 499; 0603-C-NOSILK; MPN RMCF0603FT499R
R83: 22k; 0603-C-NOSILK; MPN RMCF0603FT22K0
R84: 5.6k; 0603-C-NOSILK; MPN RMCF0603FT5K60
R87: 1k; 0603-C-NOSILK; MPN RMCF0603FT1K00
TP2, TP12, TP13, TP17, TP18, TP110, TP151: Test-Point; TestPoint-0.75mm-th
TP10, TP11, TP14, TP15, TP16, TP37, TP40: Test-Point; TestPoint_Pad_D1.0mm
U6, U36: LTC3624-5; DFN-8-1EP_3x3mm_P0.5mm_EP1.65x2.38mm_ThermalVias0.3mm; MPN LTC3624IDD-5#PBF
U31, U38: LP2985AIM5-3.3; SOT-23-5; MPN LP2985AIM5-3.3/NOPB
U34: TPS259621DDA; Texas_R-PDSO-G8_EP2.95x4.9mm_Mask2.4x3.1mm_ThermalVias; MPN TPS259621DDAT
U35: TPS259620DDA; Texas_R-PDSO-G8_EP2.95x4.9mm_Mask2.4x3.1mm_ThermalVias; MPN TPS259620DDAT

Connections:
3.3V: R85.1; also elsewhere on the board
3.3V-L: C139.1, TP2.1 (1_1), U38.5 (VOUT); also elsewhere on the board
3.3V-U: C132.1, TP151.1 (1_1), U31.5 (VOUT); also elsewhere on the board
5V: C13.1, C14.1, C15.1, L1.2, R33.2, TP110.1 (1_1), U6.5 (FB); also elsewhere on the board
5V-R: C126.1, C127.1, C128.1, FB2.1, FB3.1, L21.2, R1.2, TP18.1 (1_1), U36.5 (FB); also elsewhere on the board
/OSD3358: SIP B/RADIO_CURRENT: R86.1; also elsewhere on the board
/OSD3358: SIP C/L_BAND_ENABLE: TP40.1 (1_1), U38.3 (EN); also elsewhere on the board
/OSD3358: SIP C/RADIO_nFLT: R85.2, TP15.1 (1_1), U35.6 (*FLT); also elsewhere on the board
/OSD3358: SIP C/UHF_ENABLE: TP37.1 (1_1), U31.3 (EN); also elsewhere on the board
/OSD3358: SIP D/RADIO_ENABLE: R3.1, TP14.1 (1_1), U35.3 (EN/UVLO); also elsewhere on the board
/Power/VBUSP-RADIO: C123.1, C124.1, TP17.1 (1_1), U35.5 (OUT), U36.2 (Vin), U36.3 (RUN)
GND: C5.2, C6.2, C7.2, C10.2, C13.2, C14.2, C15.2, C47.2, C52.2, C53.2, C74.2, C99.2, C100.2, C101.2, C122.2, C123.2, C124.2, C125.2, C126.2, C127.2, C128.2, C130.2, C132.2, C135.2, C137.2, C138.2, C139.2, D2.1 (K), D11.1 (K), R3.2, R29.2, R82.2, R84.2, R87.2, R89.2, U6.8 (GND), U6.9 (GND), U31.2 (GND), U34.1 (GND), U34.9 (GND), U35.1 (GND), U35.9 (GND), U36.8 (GND), U36.9 (GND), U38.2 (GND); also elsewhere on the board
unnamed: C47.1, FB3.2, L24.1
unnamed: C52.1, FB2.2, L23.1
unnamed: D2.2 (A), R33.1
unnamed: D11.2 (A), R1.1
unnamed: C10.1, R28.1, U6.6 (INTVcc)
unnamed: R28.2, R29.1, U6.7 (MODE)
unnamed: L1.1, U6.1 (SW)
unnamed: C135.1, U31.4 (BYPASS)
unnamed: C5.1, C130.1, L23.2, U31.1 (VIN)
unnamed: TP10.1 (1_1), U34.6 (*FLT)
unnamed: R83.2, R84.1, U34.3 (EN/UVLO)
unnamed: R82.1, TP11.1 (1_1), U34.7 (ILM)
unnamed: C99.1, U34.2 (dVdt)
unnamed: R86.2, R87.1, TP16.1 (1_1), U35.7 (ILM)
unnamed: C122.1, U35.2 (dVdt)
unnamed: C125.1, R88.1, U36.6 (INTVcc)
unnamed: R88.2, R89.1, U36.7 (MODE)
unnamed: L21.1, U36.1 (SW)
unnamed: C138.1, U38.4 (BYPASS)
unnamed: C53.1, C137.1, L24.2, U38.1 (VIN)
VBUS: C74.1, C100.1, C101.1, R83.1, TP13.1 (1_1), U34.4 (IN), U35.4 (IN); also elsewhere on the board
VBUSP: C6.1, C7.1, TP12.1 (1_1), U6.2 (Vin), U6.3 (RUN), U34.5 (OUT)

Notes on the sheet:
REMEASURE CURRENTS AND LABEL!!!!
330Ω/1.5A
1210
Vbus = (6.0, 7.2, 8.4) V
Radio Efuse
5V Card Switching Supply
Vmax = 17 V, Imax = 2 A MODE = INTVcc/2 sets cont. mode operation 1 MHz operation
0805
FUTURE: Upgrade SPS or add secondary SPS when new PA is added.
C3 should draw ~ 844 mA @ 5V
3.3V from OSD3358
All resistors are 0603 1% AEC-Q200 unless marked. All capacitors are 0603 AEC-Q200 Vw >= 16V X5R or better unless marked.
UHF Radio Supply
@ ~99 mA (150 mA max) = 168 mW
@ 108 + 99 + 430 = ~637 mA
Vmax = 17 V, Imax = 2 A MODE = INTVcc/2 sets cont. mode operation
TPS259621 = Autoretry after thermal shutdown Card current limited to 1.8 A by R_ILM = 499 ohm dv/dt = 10nF sets it to 4.2 V/ms instead of the default 70 V/ms OVLO = 13.7 V (open) UVLO = 6.0 V ~{FLT} can't do anything :)
Card EFuse
@ ~108 mA (150 mA max) = 184 mW
TPS259620 = Latch after thermal shutdown (toggle EN to reset) VBUS-RADIO is limited to 0.9 A by 1kOhm R_ILM dv/dt = 10nF sets it to 4.2 V/ms instead of the default 70 V/ms OVLO = 13.7 V (open) UVLO = 5 V
L Band Radio Supply
